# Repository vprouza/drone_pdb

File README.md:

Power Distibution board for my drone.
Designed to hold six JMT BS30D 30A 2-6S Brushless ESC and provide simple way to connect motors.

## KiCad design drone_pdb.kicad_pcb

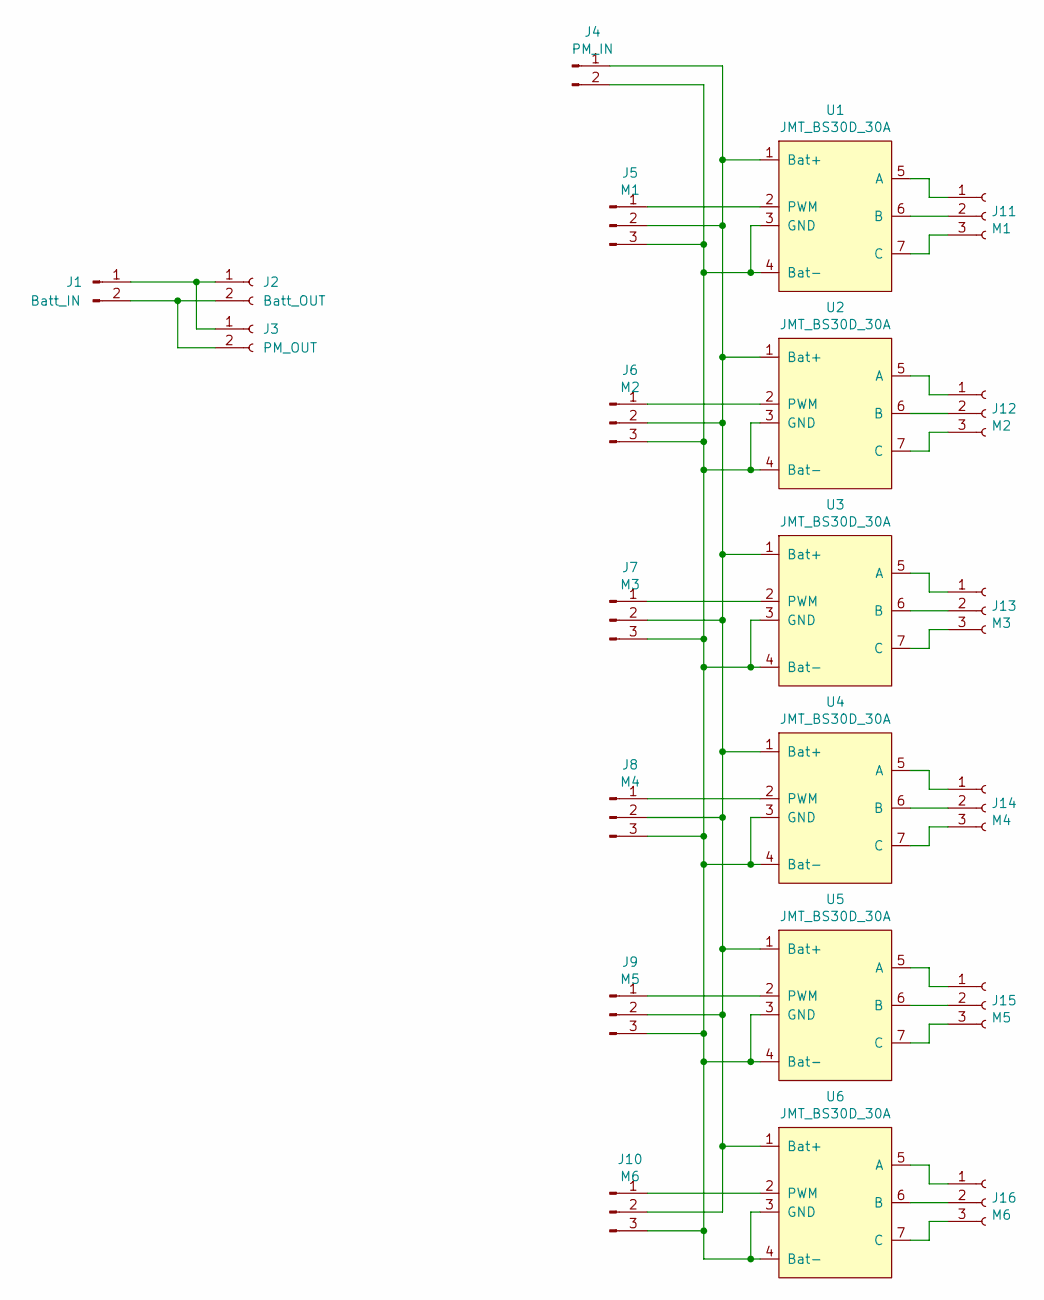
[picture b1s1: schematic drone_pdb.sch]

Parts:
J1: Batt_IN; AMASS_XT60-M_1x02_P7.20mm_Vertical
J2: Batt_OUT; AMASS_XT60-M_1x02_P7.20mm_Vertical
J3: PM_OUT; AMASS_XT60-M_1x02_P7.20mm_Vertical
J4: PM_IN; AMASS_XT60-M_1x02_P7.20mm_Vertical
J5: M1; PinHeader_1x03_P2.54mm_Vertical
J6: M2; PinHeader_1x03_P2.54mm_Vertical
J7: M3; PinHeader_1x03_P2.54mm_Vertical
J8: M4; PinHeader_1x03_P2.54mm_Vertical
J9: M5; PinHeader_1x03_P2.54mm_Vertical
J10: M6; PinHeader_1x03_P2.54mm_Vertical
J11: M1; AMASS_MR30PW-FB_1x03_P3.50mm_Horizontal
J12: M2; AMASS_MR30PW-FB_1x03_P3.50mm_Horizontal
J13: M3; AMASS_MR30PW-FB_1x03_P3.50mm_Horizontal
J14: M4; AMASS_MR30PW-FB_1x03_P3.50mm_Horizontal
J15: M5; AMASS_MR30PW-FB_1x03_P3.50mm_Horizontal
J16: M6; AMASS_MR30PW-FB_1x03_P3.50mm_Horizontal
U1, U2, U3, U4, U5, U6: JMT_BS30D_30A; BS30D

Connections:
unnamed: J1.1, J2.1, J3.1
unnamed: J1.2, J2.2, J3.2
unnamed: J5.1, U1.2 (PWM)
unnamed: J6.1, U2.2 (PWM)
unnamed: J7.1, U3.2 (PWM)
unnamed: J8.1, U4.2 (PWM)
unnamed: J9.1, U5.2 (PWM)
unnamed: J10.1, U6.2 (PWM)
unnamed: J4.1, J5.2, J6.2, J7.2, J8.2, J9.2, J10.2, U1.1 (Bat+), U2.1 (Bat+), U3.1 (Bat+), U4.1 (Bat+), U5.1 (Bat+), U6.1 (Bat+)
unnamed: J4.2, J5.3, J6.3, J7.3, J8.3, J9.3, J10.3, U1.3 (GND), U1.4 (Bat-), U2.3 (GND), U2.4 (Bat-), U3.3 (GND), U3.4 (Bat-), U4.3 (GND), U4.4 (Bat-), U5.3 (GND), U5.4 (Bat-), U6.3 (GND), U6.4 (Bat-)
unnamed: J11.1, U1.5 (A)
unnamed: J11.2, U1.6 (B)
unnamed: J11.3, U1.7 (C)
unnamed: J12.1, U2.5 (A)
unnamed: J12.2, U2.6 (B)
unnamed: J12.3, U2.7 (C)
unnamed: J13.1, U3.5 (A)
unnamed: J13.2, U3.6 (B)
unnamed: J13.3, U3.7 (C)
unnamed: J14.1, U4.5 (A)
unnamed: J14.2, U4.6 (B)
unnamed: J14.3, U4.7 (C)
unnamed: J15.1, U5.5 (A)
unnamed: J15.2, U5.6 (B)
unnamed: J15.3, U5.7 (C)
unnamed: J16.1, U6.5 (A)
unnamed: J16.2, U6.6 (B)
unnamed: J16.3, U6.7 (C)

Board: 2 copper layers, 22 parts (0 on the bottom side), 28 nets, no tracks yet.

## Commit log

2021-10-21 Created ESC symbol
2021-10-21 basic schematic
2021-10-22 Basic esc footprint
2021-10-22 Started pcb design
